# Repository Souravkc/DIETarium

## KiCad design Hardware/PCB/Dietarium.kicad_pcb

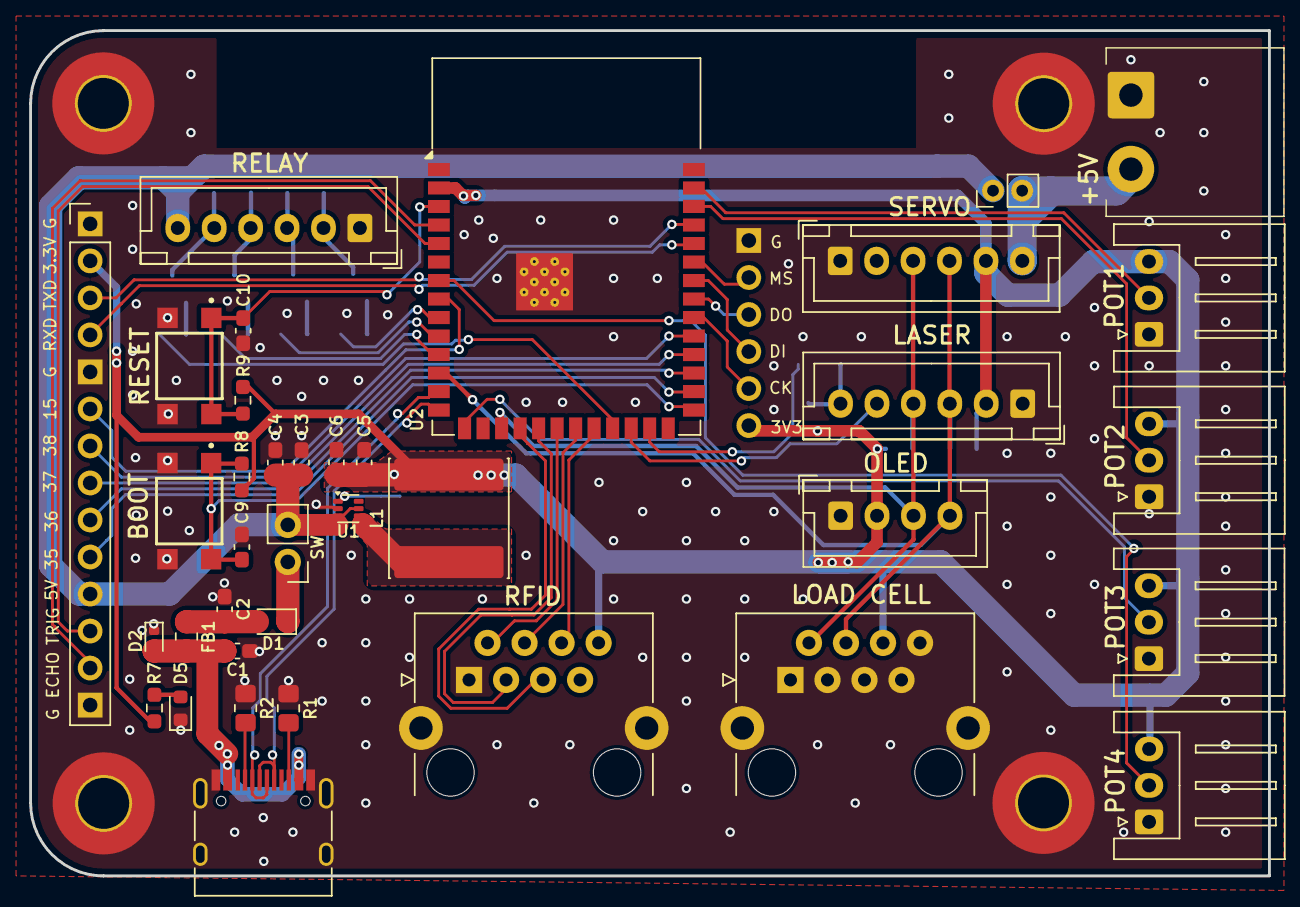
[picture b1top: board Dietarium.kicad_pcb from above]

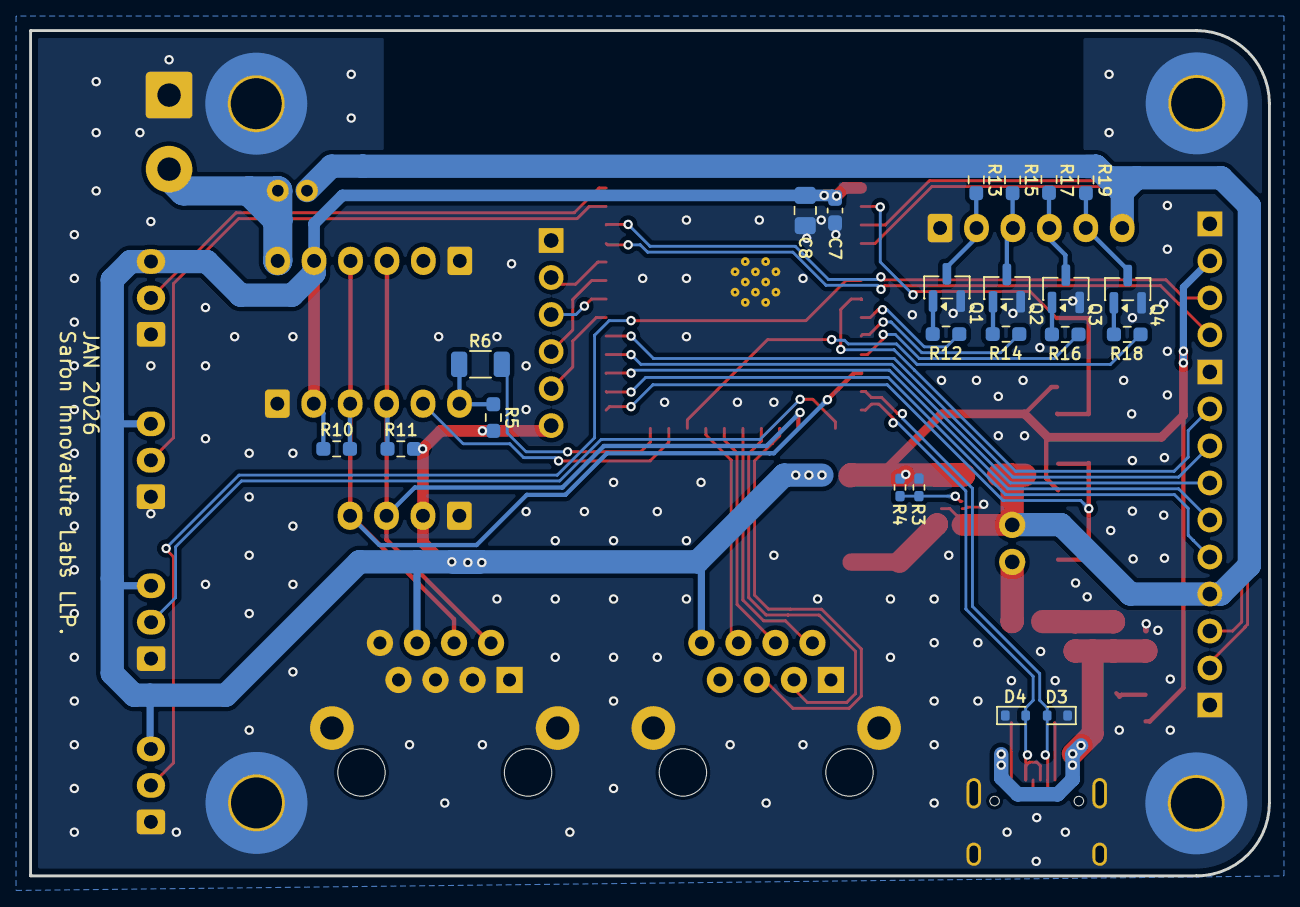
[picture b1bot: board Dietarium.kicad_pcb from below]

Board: 2 copper layers, 85.0 x 58.0 mm, 64 parts (22 on the bottom side), 55 nets.

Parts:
C1, C2, C3, C5, C7: 0.1uF; C_0603_1608Metric_Pad1.08x0.95mm_HandSolder
C4: 4.7uF; C_0603_1608Metric_Pad1.08x0.95mm_HandSolder
C6: 22uF; C_0603_1608Metric_Pad1.08x0.95mm_HandSolder
C8: 10uF; C_0805_2012Metric_Pad1.18x1.45mm_HandSolder
C9, C10: 1uF; C_0603_1608Metric_Pad1.08x0.95mm_HandSolder
D1: 1N5819WS; D_SOD-323
D2, D3, D4: LESD5D50CT1G; D_SOD-523
D5: LED; LED_0603_1608Metric
FB1: 120R; R_0805_2012Metric_Pad1.20x1.40mm_HandSolder
H1, H2, H3, H4: MountingHole_Pad; MountingHole_3.5mm_Pad_TopBottom
J1: USB_C_Receptacle_USB2.0_16P; USB_C_Receptacle_HRO_TYPE-C-31-M-12
J2: OLED; JST_XH_B4B-XH-A_1x04_P2.50mm_Vertical
J3: JTAG; PinHeader_1x06_P2.54mm_Vertical
J4: SERVO; JST_XH_B6B-XH-A_1x06_P2.50mm_Vertical
J5: RELAY MODULE; JST_XH_B6B-XH-A_1x06_P2.50mm_Vertical
J6: VL53L4CD; JST_XH_B6B-XH-A_1x06_P2.50mm_Vertical
J7: POT4; JST_XH_S3B-XH-A_1x03_P2.50mm_Horizontal
J8: POT3; JST_XH_S3B-XH-A_1x03_P2.50mm_Horizontal
J9: POT2; JST_XH_S3B-XH-A_1x03_P2.50mm_Horizontal
J10: POT1; JST_XH_S3B-XH-A_1x03_P2.50mm_Horizontal
J11: EXT PWR; Untitled
J12: Conn_01x14; PinHeader_1x14_P2.54mm_Vertical
J13: HX711; RJ45_HALO_HFJ11-x2450HRL_Horizontal
J14: RFID-RC522; RJ45_HALO_HFJ11-x2450HRL_Horizontal
JP1: Jumper_2_Open; PinHeader_1x02_P2.00mm_Vertical
JP2: ON/OFF; PinHeader_1x02_P2.54mm_Vertical
L1: SWPA8040S1R0NT; L_Sunlord_SWPA8040S
Q1, Q2, Q3, Q4: BC847; SOT-23
R1, R2: 5.1K; R_0805_2012Metric_Pad1.20x1.40mm_HandSolder
R3: 453K; R_0402_1005Metric_Pad0.72x0.64mm_HandSolder
R4: 100K; R_0402_1005Metric_Pad0.72x0.64mm_HandSolder
R5, R8, R9, R13, R15, R17, R19: 10K; R_0603_1608Metric_Pad0.98x0.95mm_HandSolder
R6: 10K; R_1206_3216Metric
R7: 1K; R_0603_1608Metric_Pad0.98x0.95mm_HandSolder
R10, R11, R12, R14, R16, R18: 2.2K; R_0603_1608Metric_Pad0.98x0.95mm_HandSolder
S1: RESET; SW_SWT0211-050010GSA_REVA
S2: BOOT; SW_SWT0211-050010GSA_REVA
U1: TLV62569ADRL; SOT-563
U2: ESP32-S3-WROOM-1

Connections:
/3.3V: C5.1, C6.1, C7.1, C8.1, J2.2, J3.6, J4.5, J6.2, J7.3, J8.3, J9.3, J10.3, J12.2, J13.6, J14.8, L1.2, R3.1, R5.1, R7.1, R8.1, R9.1, R10.1, R11.1, U2.2 (3V3)
/5V: C3.1, C4.1, J5.6, J12.11, JP1.1 (A), JP2.2 (B), R13.1, R15.1, R17.1, R19.1, U1.3 (VIN), U1.5 (EN)
/5V_USB: D1.1 (K), JP2.1 (A)
/ADC1_CH0: J10.2, U2.39 (IO1)
/ADC1_CH1: J9.2, U2.38 (IO2)
/ADC1_CH2: J8.2, U2.15 (IO3)
/ADC1_CH6: J7.2, U2.7 (IO7)
/BOOT: C9.1, R8.2, S2.1, S2.2, U2.27 (IO0)
/ECHO: J12.13, U2.4 (IO4)
/ENABLE: C10.1, R9.2, S1.1, S1.2, U2.3 (EN)
/IN1: R12.2, U2.9 (IO16)
/IN2: R14.2, U2.10 (IO17)
/IN3: R16.2, U2.11 (IO18)
/IN4: R18.2, U2.23 (IO21)
/IO15: J12.6, U2.8 (IO15)
/IO35: J12.10, U2.28 (IO35)
/IO36: J12.9, U2.29 (IO36)
/IO37: J12.8, U2.30 (IO37)
/IO38: J12.7, U2.31 (IO38)
/MISO: J14.4, U2.21 (IO13)
/MOSI: J14.3, U2.19 (IO11)
/MTCK: J3.5, U2.32 (IO39)
/MTDI: J3.4, U2.34 (IO41)
/MTDO: J3.3, U2.33 (IO40)
/MTMS: J3.2, U2.35 (IO42)
/RLY1: J5.2, Q1.3 (C), R13.2
/RLY2: J5.3, Q2.3 (C), R15.2
/RLY3: J5.4, Q3.3 (C), R17.2
/RLY4: J5.5, Q4.3 (C), R19.2
/RST: J14.6, U2.22 (IO14)
/RXD: J12.4, U2.36 (RXD0)
/SCK: J14.2, U2.20 (IO12)
/SCL: J2.3, J4.3, J6.4, J13.2, R11.2, U2.17 (IO9)
/SDA: J2.4, J4.4, J6.3, J13.4, R10.2, U2.12 (IO8)
/SS: J14.5, U2.18 (IO10)
/TRIG: J12.12, U2.5 (IO5)
/TXD: J12.3, U2.37 (TXD0)
/USB_D+: D4.2 (A2), J1.A6 (D+), J1.B6 (D+), U2.14 (USB_D+)
/USB_D-: D3.2 (A2), J1.A7 (D-), J1.B7 (D-), U2.13 (USB_D-)
/V+: J4.6, J11.2, JP1.2 (B)
/~INT: J6.5, U2.24 (IO47)
/~SHUT: R6.2, U2.25 (IO48)
GND: C1.2, C2.2, C3.2, C4.2, C5.2, C6.2, C7.2, C8.2, C9.2, C10.2, D2.1 (A1), D3.1 (A1), D4.1 (A1), D5.1 (K), H1.1, H2.1, H3.1, H4.1, J1.A1 (GND), J1.A12 (GND), J1.B1 (GND), J1.B12 (GND), J1.S1 (SHIELD), J2.1, J3.1, J4.1, J5.1, J6.1, J7.1, J8.1, J9.1, J10.1, J11.1, J12.1, J12.5, J12.14, J13.1, J13.3, J13.5, J13.7, J13.8, J13.SH, J14.1, J14.SH, Q1.2 (E), Q2.2 (E), Q3.2 (E), Q4.2 (E), R1.2, R2.2, R4.2, S1.3, S1.4, S2.3, S2.4, U1.2 (GND), U2.1 (GND), U2.40 (GND), U2.41 (GND)
unnamed: C2.1, D1.2 (A), FB1.2
unnamed: C1.1, D2.2 (A2), FB1.1, J1.A4 (VBUS), J1.A9 (VBUS), J1.B4 (VBUS), J1.B9 (VBUS)
unnamed: D5.2 (A), R7.2
unnamed: J1.A5 (CC1), R2.1
unnamed: J1.B5 (CC2), R1.1
unnamed: J6.6, R5.2, R6.1
unnamed: Q1.1 (B), R12.1
unnamed: Q2.1 (B), R14.1
unnamed: Q3.1 (B), R16.1
unnamed: Q4.1 (B), R18.1
unnamed: R3.2, R4.1, U1.1 (FB)
unnamed: L1.1, U1.4 (SW)

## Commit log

2026-01-20 initial project upload
